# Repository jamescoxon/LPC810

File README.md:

Adapted from LPC810_CodeBase

* Updated SPI driver
* New driver for RFM69 Radio module
* UART code using interrupt and buffer
* GPS code to read Ublox GPS modules
* Stripped down version of string library
* Included memcpy

Please remember to edit src/main.c and add your own node ID and location string.

LPC810_CodeBase
===============

Open source code base for the ARM Cortex M0+ LPC810 family from NXP.

This code base is intended to work with the LPC810 in a DIP8 package.  While these drivers are based on the original LPC800 example code from NXP, the LPC810 has limited resources (4KB flash and 1KB SRAM), so smaller, lighter-weight drivers had to be written to get the most out of these resources we have.

The current code implements the following peripheral drivers:

- A basic SPI driver
- Some simple GPIO helper functions (although GPIO should normally be accessed directly via the appropriate registers)
- A simple driver for UART0 and printf-redirection that allows 'printf' output to be transmitted to UART0
- A basic multi-rate timer driver that allows us to set delays

The code base also implements a mini printf that takes up much less space than the default printf used in most libc variants.  If necessary, it's easy to change the printf redirection to a location other than UART0 via the printf-redirection.c file.

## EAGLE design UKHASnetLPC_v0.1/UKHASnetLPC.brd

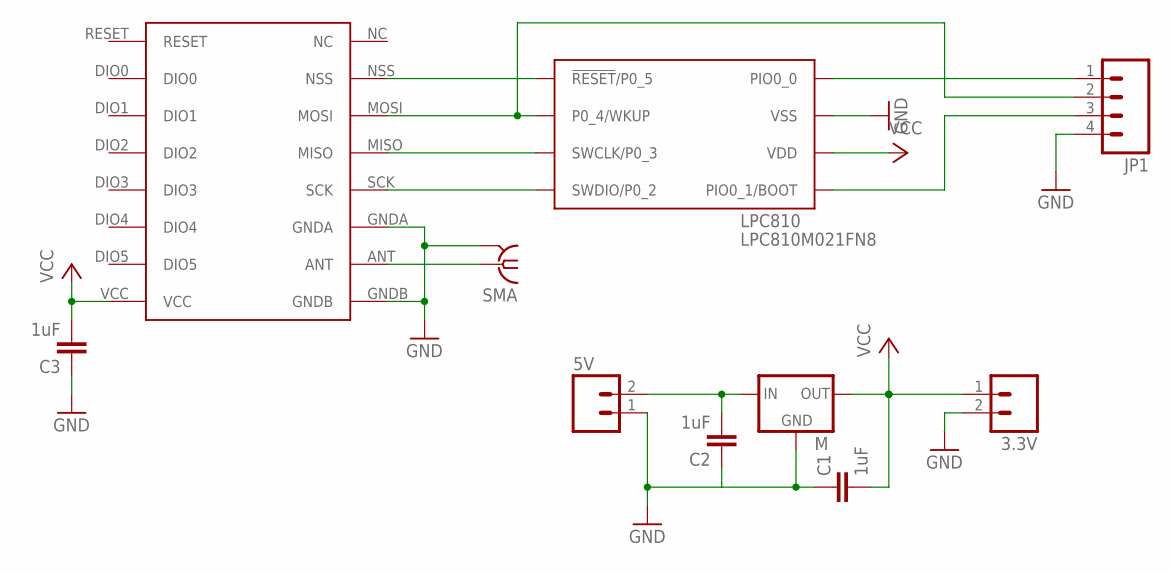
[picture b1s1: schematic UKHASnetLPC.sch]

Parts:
3.3V, 5V: M02LOCK; 1X02_LOCK
C1, C2, C3: 1uF; CAP-PTH-SMALL
JP1: M04PTH; 1X04
LPC810: LPC810M021FN8; DIP8
M: MCP1700INLINE; TO92-INLINE
RFM69: RFM69HW; RFM
SMA: BUS-SMA

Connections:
GND: 3.3V.2, 5V.1, C1.1, C2.1, C3.1, JP1.4, LPC810.P$7 (VSS), M.1 (GND), RFM69.GNDA, RFM69.GNDB, SMA.2 (GND), SMA.3 (GND), SMA.4 (GND), SMA.5 (GND)
unnamed: LPC810.P$1 (!RESET!/P0_5), RFM69.NSS
unnamed: JP1.2, LPC810.P$2 (P0_4/WKUP), RFM69.MOSI
unnamed: LPC810.P$3 (SWCLK/P0_3), RFM69.MISO
unnamed: LPC810.P$4 (SWDIO/P0_2), RFM69.SCK
unnamed: JP1.3, LPC810.P$5 (PIO0_1/BOOT)
unnamed: JP1.1, LPC810.P$8 (PIO0_0)
unnamed: RFM69.ANT, SMA.1
unnamed: 5V.2, C2.2, M.2 (IN)
VCC: 3.3V.1, C1.2, C3.2, LPC810.P$6 (VDD), M.3 (OUT), RFM69.VCC

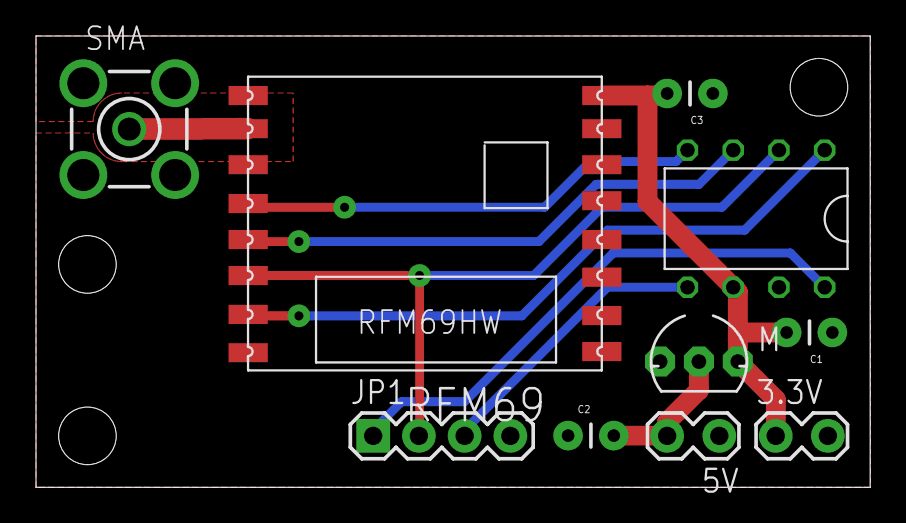
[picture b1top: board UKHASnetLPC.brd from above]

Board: 4 copper layers, 46.3 x 25.1 mm, 10 parts (0 on the bottom side), 10 nets.

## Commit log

2014-06-03 added code
2014-06-03 merged Synchronus RFM69 lib with current code
2014-06-03 currently is correctly rx'ing data and printing. Appears to be transmitting but not yet confirmed working
2014-06-03 suggestions to improve fifowrite
2014-06-19 working rx and tx, increases packet count appropriately. Needs work on buffer sizes and also optimisation.
2014-06-24 added new string.c with string function taken from minilib-c project. With string functions able to add repeat functions. Now have lpc810 repeating strings!
2014-06-25 removed printf to save space
2014-06-27 reduced size of string.c to save space
2014-06-27 removed a few more defines that weren't required
2014-07-24 updated to work on LPC810 PCB boards (UKHASnet 0.1).
2014-07-25 added internal temperature from the RFM69 so that node actually has data to transmit. Previously it was float but switched to int to save space. all running on new UKHASnet node
2014-07-25 added define to comment out printing to serial to save space
2014-08-17 added rest of codebase to repos
2014-08-19 added working GPS code (tested on BALL1) and then added a define to comment out the GPS specific code.
2014-08-19 removed RFM69.cpp as not required
2014-08-20 added eagle files
2014-08-21 updated to print own strings
2014-08-21 Changed ID and location
2014-08-21 changed include to lower case as wouldn't work on linux (though strangely worked on OS X )
2014-08-21 Change include to lower case
2014-08-22 added variable to control gap between tx and added comment about how to change this
2014-08-22 switched it from unit8_t to int to allow larger values
2014-08-23 added DL7AD's changes to try and remove current tx bugs
2014-08-23 changed ID to NODE_ID and also allowed changes to output power easily
2014-08-24 adapted processing function, switched to using sprintf instead of strcat
2014-08-24 Redesigned board to avoid interference
2014-08-25 reversed changes that broke data processing, rolled back to old version of code - now working again
2014-08-25 fixed bug that was causing node to transmit for too long (in the FiFo write it was overflowing). now more reliable as well as completely transmitting the first string with out the dodgey hack
2014-08-25 reduced freq of transmissions as now not need for testing
2014-08-26 Added serial transmission functions
2014-08-30 set default to XXX
2014-09-01 fixed bug found by Mark where the serial was being setup with 9600 for both GPS and non-GPS modes rather than 115200
2014-09-02 FIXED bug where repeated packet was actually only at 10mW rather than the pre-defined POWER_OUTPUT. This would explain on the test flight EMF14 we only downlinked packets and didn't get repeated pack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
2014-09-02 added random number generator (well sort of) and then added random delays to avoid packet clashes
2014-09-02 added random delay and tested code - appears to be working
2014-09-03 switched \n\r to \r\n to allow python to work better (upload scripts etc)
2014-09-03 added RSSI reporting in the serial debug - allows RSSI to be reported to the server to help work stuff out in the future
2014-09-04 Currently reports last rssi in packet but not to console - seems to hang if printf of rssi - unsure why. also have added another define to comment out serial in as not always required.
2014-09-11 Print git version at startup
2014-09-11 Ensure main is rebuilt if git version changes
2014-09-11 updated main.c and added rssi for noise floor
2014-09-14 added new adc feature
2014-09-14 added adc.c and adc.h
2014-09-22 activated debug
2014-10-18 Restructured to remove forward reference warnings
2014-10-18 Removed duplicate declaration of _buf
2014-10-18 Increased stack size ( qyx_ suggestion was correct )
2014-10-30 Fix register bit tests in RFM69_readTemp and RFM69_sampleRssi
2014-10-30 Adjust RSSI threshold to 4dB above measured noise floor
2014-10-30 Add RSSI to rx debug (gateway) string
2014-10-30 Guard against RSSI measurement not completing
2014-10-30 Add function to read last RSSI threshold
2014-10-30 Restart rx if it spends too long in RxReady without reaching PayloadReady. Add diagnostics to monitor this behaviour.
2014-11-24 Incrementally adjust threshold to 3dB above noise floor
2014-11-24 Use hardware timeout to determine when to restart receiver.
2015-04-09 working adc, though not really connecting now to network - needs investigating...
2015-04-14 small changes in freq
2015-04-14 reverted freq changes, working well currently on my last remaining LPC810 board!
2015-04-14 updated RFM69Config to latest arduino firmware settings
2015-04-14 tidied up a bit
2015-04-14 increased stack size, now gateway passes its own messages (therefore if the rest of network goes down still know its running) code currently running on AB node
2015-04-18 moved the node settings to a seperate file to allow easy management of main.c
2015-04-18 added two packet validity checks, 1 - checks first char is a number, 2 checks second is a letter
2015-04-18 now compares decimal rather then char itself to allow for a range
2015-04-18 made the code slightly more tidy
2015-04-19 fixed packet checking code, now parses the first 2 chars to ensure they are valid (number followed by a lower case letter) - working code
2015-04-19 reverted settings to generic
2015-04-29 created settings.h.example, removed averaging adc result as read_adc2 already does this
2015-04-29 tidied up the packet formation in main.c (with regards to lots of different ifdef etc.
2015-04-29 added a .gitignore file now
2015-04-29 added zombie mode, where instead of listening for packets the radio is put to sleep inbetween Tx, will conserve significant power
2015-04-29 code tidying, some functions currently won't fit in flash, needs some pruning
2015-05-15 added more zombie mode
2015-05-20 added new BrownOut define with code from Jeelabs for the LPC810 to measure its own input voltage (don't think it can be used with the adc code activated). Now that it can set its BOD functions it'll 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
2015-05-25 fixed brownout power saving, if input V drops below threshold then will sleep a bit longer to allow the cap to charge up fully. Need to fix teh temperature reading, if in zombie it doesn't read the a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
2015-05-25 moved sleep and zombie functions to zombie.c to make things easier
2015-05-25 fixed temperature sensor issue, wasn't giving enough time for the RFM69's mode to change before reading the sensor. Also added BrownOut define to allow access to new code.
2015-05-27 reduced the voltage before transmitting as otherwise node gets stuck in a grey zone of txing, sometimes its good to drain the cap fully and reset everything...
2015-06-21 simplified code further, tested current consumption, can't seem to get it below about 1.5mA
2015-06-21 added some additional sleeps in an attempt to prolong the life of the node, only works if BrownOut defined, won't effect normal function of a repeater LPC node
2015-06-21 fixed sleep bug, current code running on AH4

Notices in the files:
parts and their libraries:
SparkFun-Connectors: Licensing: CC v3.0 Share-Alike You are welcome to use this library for commercial purposes.
